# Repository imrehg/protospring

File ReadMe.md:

# ProtoSpring

Prototyping board for the [VIA VAB-600 Springboard][vab600]. Schematics
and PCB done in KiCad.

## Information

For more information on this hardware, you can contact at <gergely@imreh.net>.

## Bugs, modifications

If you find any bugs on the board or want to suggest improvements, I'm always
happy to hear. Either submit an Issue on Github, or send me an email.

## License

This hardware is provided under the [CERN Open Hardware License 1.2][ohl].
The license text is included in `cern_ohl_v_1_2.txt` of this package.

[vab600]: http://www.viaspringboard.com "VIA Springboard site"
[ohl]: http://www.ohwr.org/documents/294 "CERN OHL VERSION 1.2"

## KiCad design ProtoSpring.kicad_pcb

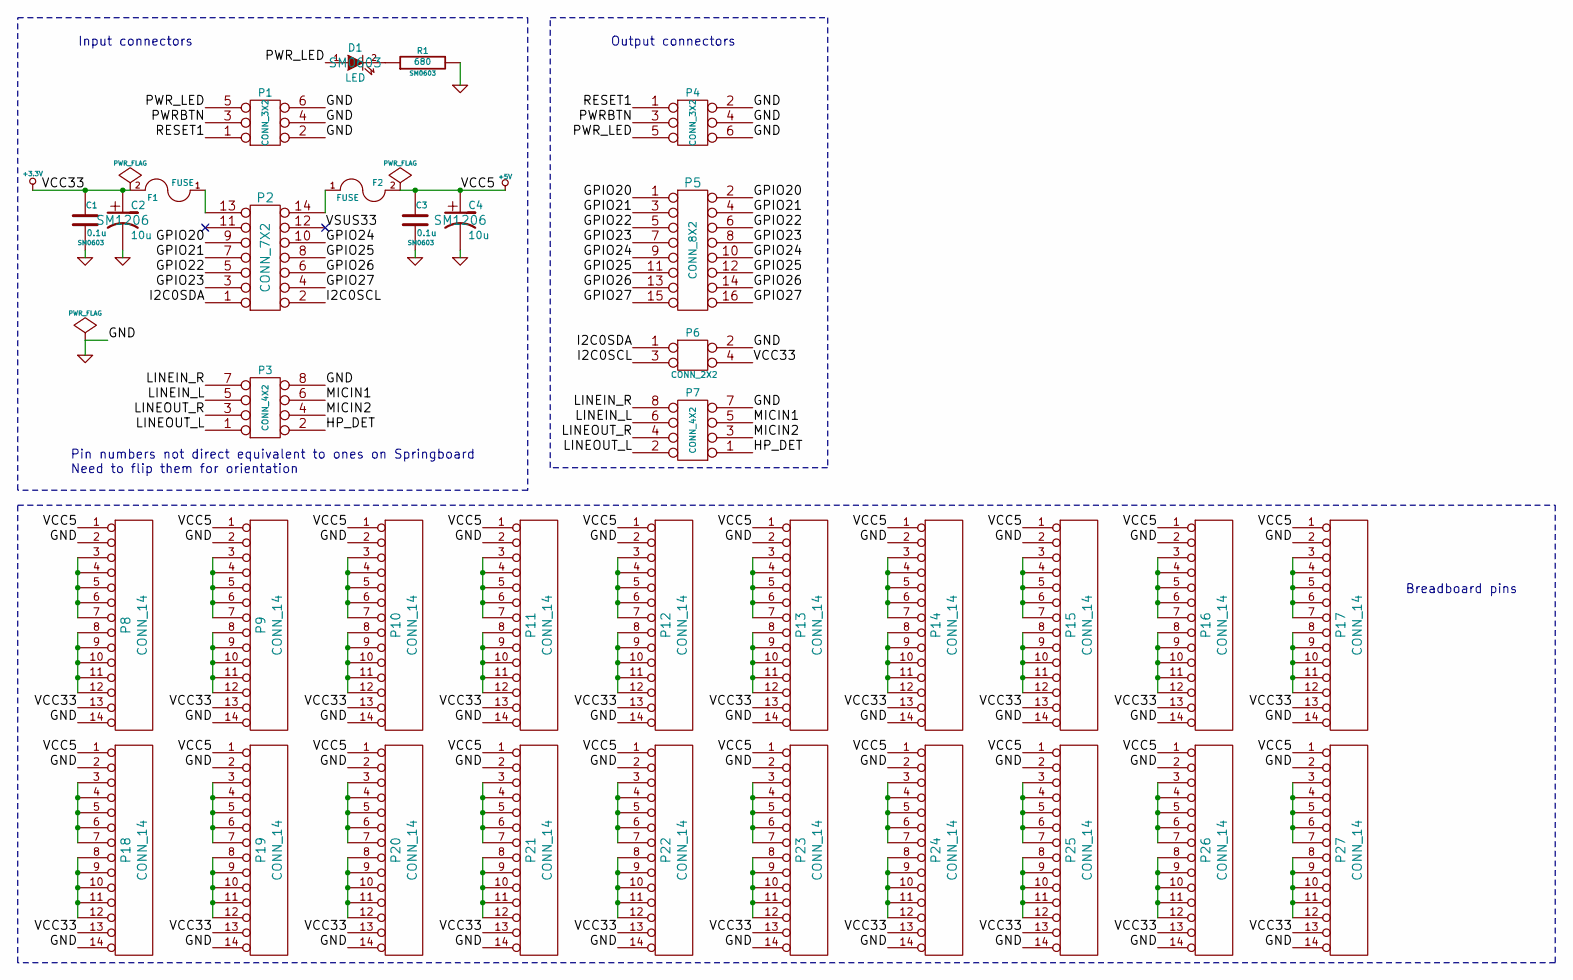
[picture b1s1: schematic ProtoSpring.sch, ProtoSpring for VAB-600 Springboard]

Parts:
C1, C3: 0.1u; SM0603; PartNumber 0603YC104KAT2A
C2, C4: 10u; SM1206; PartNumber F931A106KAA
D1: LED; SM0603; PartNumber LB Q39G-L2N2-35-1
F1, F2: FUSE; SMD1206; PartNumber 1206L110THYR
P1: CONN_3X2; Part# 950406-5002-AR
P2: CONN_7X2; Part# 950414-5002-AR
P3: CONN_4X2; Part# 950408-5002-AR
P4: CONN_3X2
P5: CONN_8X2
P6: CONN_2X2
P7: CONN_4X2
P8, P9, P10, P11, P12, P13, P14, P15, P16, P17, P18, P19, P20, P21, P22, P23, P24, P25, P26, P27: CONN_14
R1: 680; SM0603; Part# CRCW0603680RFKEA

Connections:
+3.3V: C1.1, C2.1, F1.2, P6.4, P8.13, P9.13, P10.13, P11.13, P12.13, P13.13, P14.13, P15.13, P16.13, P17.13, P18.13, P19.13, P20.13, P21.13, P22.13, P23.13, P24.13, P25.13, P26.13, P27.13
+5V: C3.1, C4.1, F2.2, P8.1, P9.1, P10.1, P11.1, P12.1, P13.1, P14.1, P15.1, P16.1, P17.1, P18.1, P19.1, P20.1, P21.1, P22.1, P23.1, P24.1, P25.1, P26.1, P27.1
/GPIO20: P2.9, P5.1, P5.2
/GPIO21: P2.7, P5.3, P5.4
/GPIO22: P2.5, P5.5, P5.6
/GPIO23: P2.3, P5.7, P5.8
/GPIO24: P2.10, P5.9, P5.10
/GPIO25: P2.8, P5.11, P5.12
/GPIO26: P2.6, P5.13, P5.14
/GPIO27: P2.4, P5.15, P5.16
/HP_DET: P3.2, P7.1
/I2C0SCL: P2.2, P6.3
/I2C0SDA: P2.1, P6.1
/LINEIN_L: P3.5, P7.6
/LINEIN_R: P3.7, P7.8
/LINEOUT_L: P3.1, P7.2
/LINEOUT_R: P3.3, P7.4
/MICIN1: P3.6, P7.5
/MICIN2: P3.4, P7.3
/PWRBTN: P1.3, P4.3
/PWR_LED: D1.1 (A), P1.5, P4.5
/RESET1: P1.1, P4.1
GND: C1.2, C2.2, C3.2, C4.2, P1.2, P1.4, P1.6, P3.8, P4.2, P4.4, P4.6, P6.2, P7.7, P8.2, P8.14, P9.2, P9.14, P10.2, P10.14, P11.2, P11.14, P12.2, P12.14, P13.2, P13.14, P14.2, P14.14, P15.2, P15.14, P16.2, P16.14, P17.2, P17.14, P18.2, P18.14, P19.2, P19.14, P20.2, P20.14, P21.2, P21.14, P22.2, P22.14, P23.2, P23.14, P24.2, P24.14, P25.2, P25.14, P26.2, P26.14, P27.2, P27.14, R1.2
unnamed: P18.8, P18.9, P18.10, P18.11, P18.12
unnamed: P19.3, P19.4, P19.5, P19.6, P19.7
unnamed: P19.8, P19.9, P19.10, P19.11, P19.12
unnamed: P18.3, P18.4, P18.5, P18.6, P18.7
unnamed: P20.8, P20.9, P20.10, P20.11, P20.12
unnamed: P20.3, P20.4, P20.5, P20.6, P20.7
unnamed: P15.8, P15.9, P15.10, P15.11, P15.12
unnamed: P14.8, P14.9, P14.10, P14.11, P14.12
unnamed: P15.3, P15.4, P15.5, P15.6, P15.7
unnamed: P17.3, P17.4, P17.5, P17.6, P17.7
unnamed: P17.8, P17.9, P17.10, P17.11, P17.12
unnamed: P16.3, P16.4, P16.5, P16.6, P16.7
unnamed: P16.8, P16.9, P16.10, P16.11, P16.12
unnamed: P25.8, P25.9, P25.10, P25.11, P25.12
unnamed: P25.3, P25.4, P25.5, P25.6, P25.7
unnamed: P27.3, P27.4, P27.5, P27.6, P27.7
unnamed: P27.8, P27.9, P27.10, P27.11, P27.12
unnamed: P26.3, P26.4, P26.5, P26.6, P26.7
unnamed: P26.8, P26.9, P26.10, P26.11, P26.12
unnamed: P22.3, P22.4, P22.5, P22.6, P22.7
unnamed: P22.8, P22.9, P22.10, P22.11, P22.12
unnamed: P21.3, P21.4, P21.5, P21.6, P21.7
unnamed: P21.8, P21.9, P21.10, P21.11, P21.12
unnamed: P24.3, P24.4, P24.5, P24.6, P24.7
unnamed: P24.8, P24.9, P24.10, P24.11, P24.12
unnamed: P23.3, P23.4, P23.5, P23.6, P23.7
unnamed: P23.8, P23.9, P23.10, P23.11, P23.12
unnamed: F2.1, P2.14
unnamed: F1.1, P2.13
unnamed: D1.2 (K), R1.1
unnamed: P12.3, P12.4, P12.5, P12.6, P12.7
unnamed: P12.8, P12.9, P12.10, P12.11, P12.12
unnamed: P11.3, P11.4, P11.5, P11.6, P11.7
unnamed: P11.8, P11.9, P11.10, P11.11, P11.12
unnamed: P14.3, P14.4, P14.5, P14.6, P14.7
unnamed: P13.3, P13.4, P13.5, P13.6, P13.7
unnamed: P13.8, P13.9, P13.10, P13.11, P13.12
unnamed: P8.8, P8.9, P8.10, P8.11, P8.12
unnamed: P9.3, P9.4, P9.5, P9.6, P9.7
unnamed: P9.8, P9.9, P9.10, P9.11, P9.12
unnamed: P8.3, P8.4, P8.5, P8.6, P8.7
unnamed: P10.3, P10.4, P10.5, P10.6, P10.7
unnamed: P10.8, P10.9, P10.10, P10.11, P10.12

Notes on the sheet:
Input connectors
Output connectors
Breadboard pins
Pin numbers not direct equivalent to ones on Springboard Need to flip them for orientation

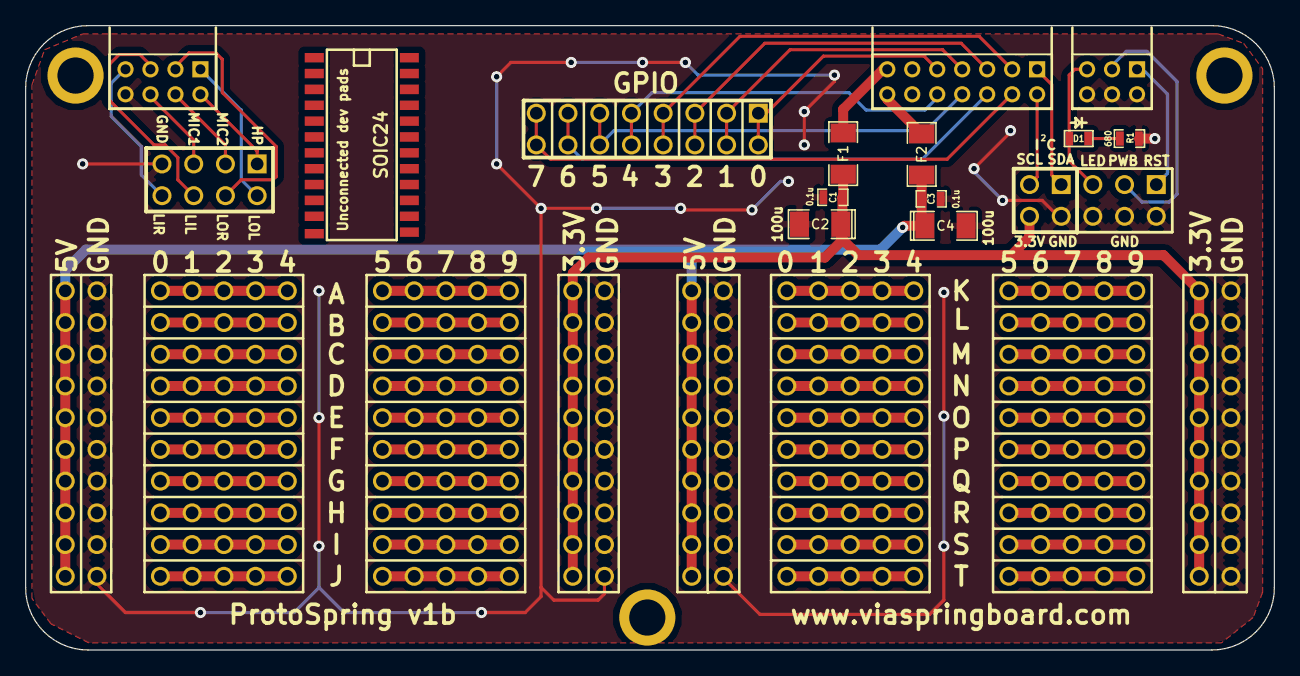
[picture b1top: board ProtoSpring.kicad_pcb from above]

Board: 2 copper layers, 100.0 x 50.0 mm, 39 parts (0 on the bottom side), 66 nets.

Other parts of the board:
MOUNT_HOLE_1, MOUNT_HOLE_2, MOUNT_HOLE_3: Val**; MOUNTING_HOLE_M25
SOIC24: VAL**; SOIC24

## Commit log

2014-11-06 updated output
2014-11-06 add readme
2014-11-06 add bugs info
2014-11-07 add BOM
2014-11-09 update schematics and pcb with some lessons learned
    Brief changelog:
    * add manufacturers and part numbers for recommended parts
    * change current limiting resistor for LED to fit its current requirements
    * update PCB with new resistor value
2014-11-09 update BOM
2014-11-14 adjusting the paths for the Audio headers
2014-11-14 add missing path back for vias
2014-11-14 add BOM table
2014-12-05 bugfix: i2c lines labeling
    The SDA and SCL lines were mixed up on the silkscreen. Fix their
    labels and update version number on the board to reflect this change.
2015-06-26 latest changes

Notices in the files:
ProtoSpring.kicad_pcb:
CERN OHL 1.2
